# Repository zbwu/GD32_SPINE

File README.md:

# GD32_SPINE

使用GD32C103的SPIne板，和CyberDog上面的SPIne板实现兼容

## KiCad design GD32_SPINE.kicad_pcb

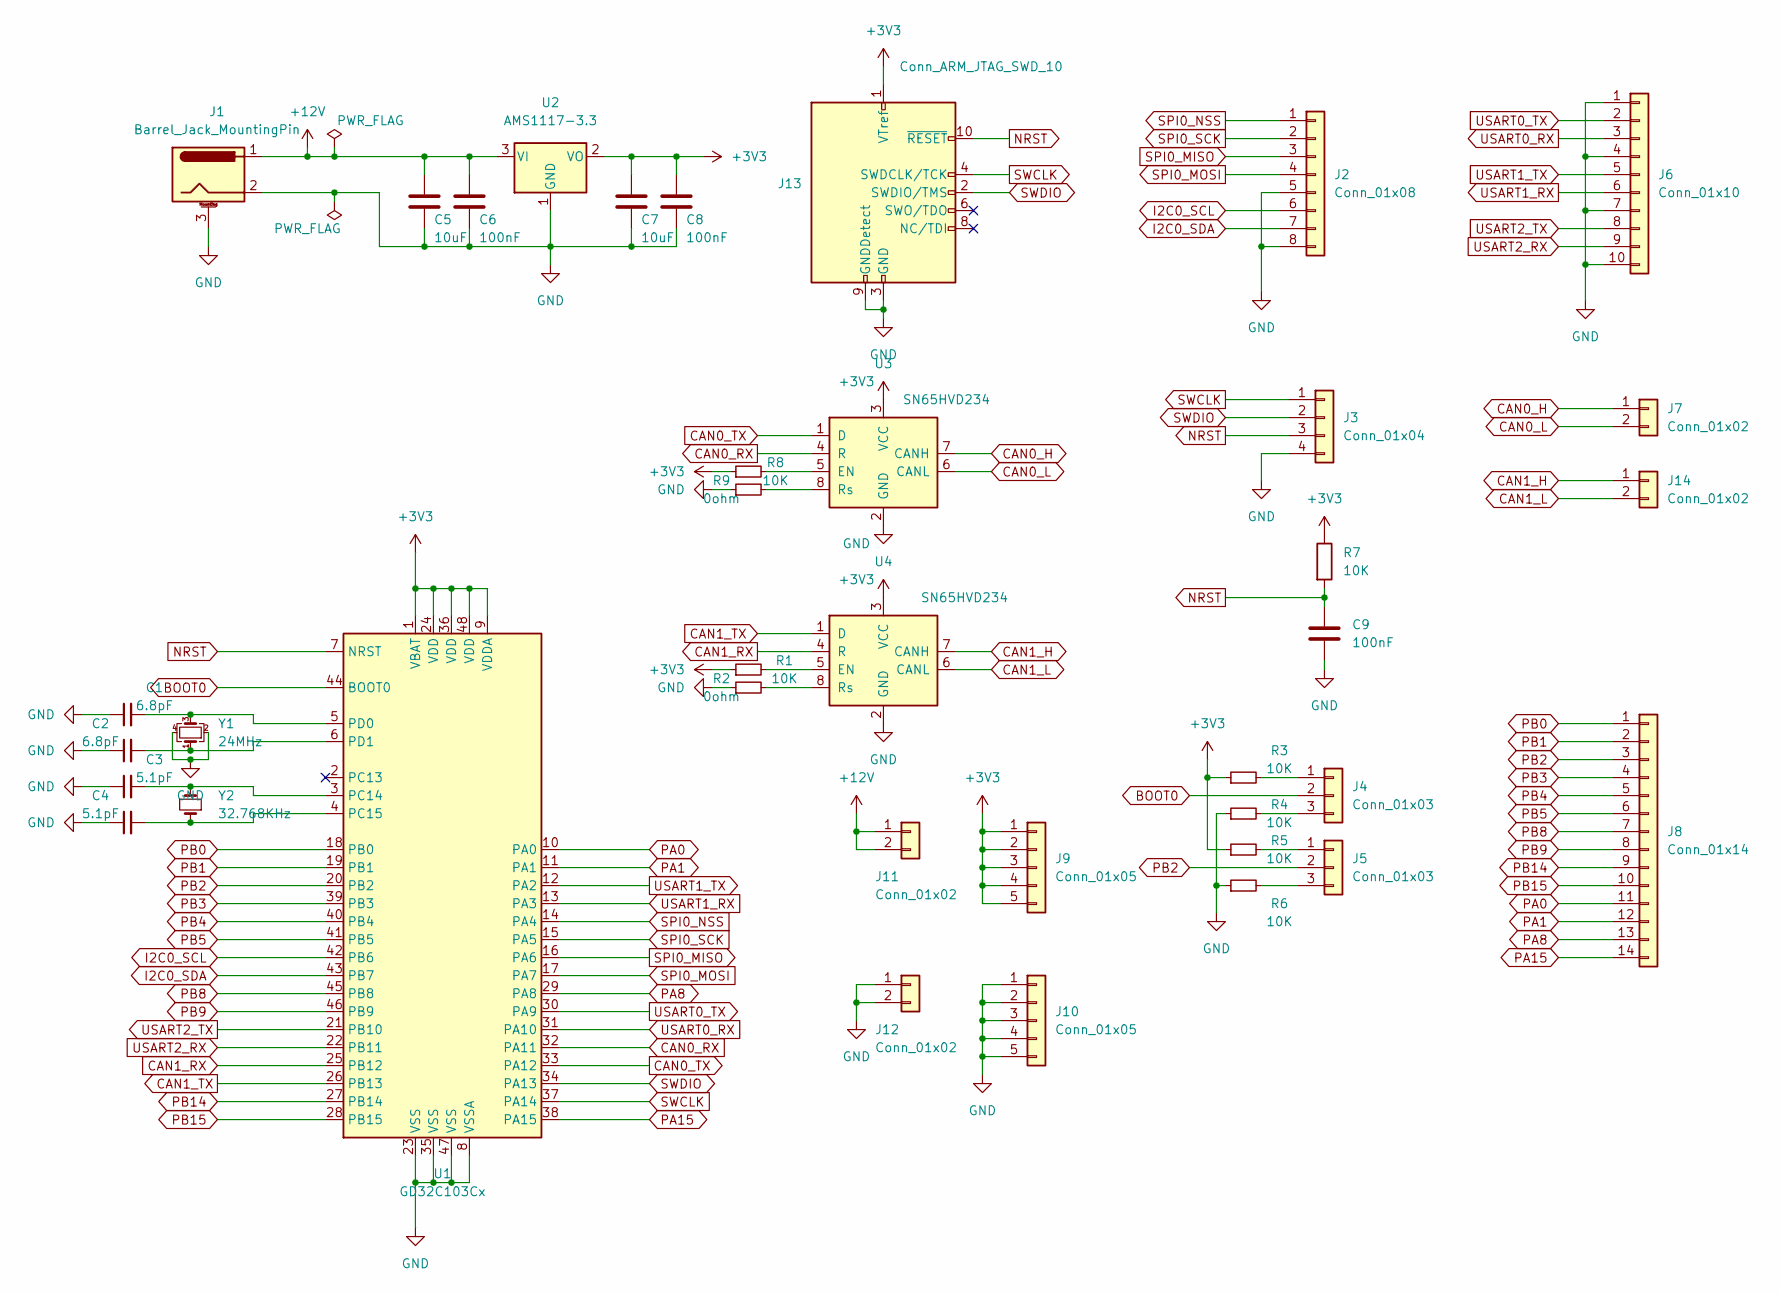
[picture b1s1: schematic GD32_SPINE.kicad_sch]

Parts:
C1, C2: 6.8pF; C_0603_1608Metric_Pad1.08x0.95mm_HandSolder
C3, C4: 5.1pF; C_0603_1608Metric_Pad1.08x0.95mm_HandSolder
C5, C7: 10uF; C_1206_3216Metric_Pad1.33x1.80mm_HandSolder
C6, C8, C9: 100nF; C_0603_1608Metric_Pad1.08x0.95mm_HandSolder
J1: Barrel_Jack_MountingPin; BarrelJack_GCT_DCJ200-10-A_Horizontal
J2: Conn_01x08; PinHeader_1x08_P2.54mm_Vertical
J3: Conn_01x04; PinHeader_1x04_P2.54mm_Vertical
J4, J5: Conn_01x03; PinHeader_1x03_P2.54mm_Vertical
J6: Conn_01x10; PinHeader_1x10_P2.54mm_Vertical
J7, J11, J12, J14: Conn_01x02; PinHeader_1x02_P2.54mm_Vertical
J8: Conn_01x14; PinHeader_1x14_P2.54mm_Vertical
J9, J10: Conn_01x05; PinHeader_1x05_P2.54mm_Vertical
J13: Conn_ARM_JTAG_SWD_10; PinHeader_2x05_P1.27mm_Vertical
R1, R3, R4, R5, R6, R7, R8: 10K; C_0603_1608Metric_Pad1.08x0.95mm_HandSolder
R2, R9: 0ohm; C_0603_1608Metric_Pad1.08x0.95mm_HandSolder
U1: GD32C103Cx; LQFP-48_7x7mm_P0.5mm
U2: AMS1117-3.3; SOT-223-3_TabPin2
U3, U4: SN65HVD234; SOIC-8_3.9x4.9mm_P1.27mm
Y1: 24MHz; Crystal_SMD_3225-4Pin_3.2x2.5mm
Y2: 32.768KHz; Crystal_SMD_3215-2Pin_3.2x1.5mm

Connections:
+3V3: C7.1, C8.1, J9.1, J9.2, J9.3, J9.4, J9.5, J13.1 (VTref), R1.1, R3.1, R5.1, R7.1, R8.1, U1.1 (VBAT), U1.9 (VDDA), U1.24 (VDD), U1.36 (VDD), U1.48 (VDD), U2.2 (VO), U3.3 (VCC), U4.3 (VCC)
+12V: C5.1, C6.1, J1.1, J11.1, J11.2, U2.3 (VI)
BOOT0: J4.2, U1.44 (BOOT0)
CAN0_H: J7.1, U3.7 (CANH)
CAN0_L: J7.2, U3.6 (CANL)
CAN0_RX: U1.32 (PA11), U3.4 (R)
CAN0_TX: U1.33 (PA12), U3.1 (D)
CAN1_H: J14.1, U4.7 (CANH)
CAN1_L: J14.2, U4.6 (CANL)
CAN1_RX: U1.25 (PB12), U4.4 (R)
CAN1_TX: U1.26 (PB13), U4.1 (D)
GND: C1.1, C2.1, C3.1, C4.1, C5.2, C6.2, C7.2, C8.2, C9.2, J1.2, J1.3, J2.5, J2.8, J3.4, J6.1, J6.4, J6.7, J6.10, J10.1, J10.2, J10.3, J10.4, J10.5, J12.1, J12.2, J13.3 (GND), J13.5 (GND), J13.9 (GNDDetect), R2.1, R4.1, R6.1, R9.1, U1.8 (VSSA), U1.23 (VSS), U1.35 (VSS), U1.47 (VSS), U2.1 (GND), U3.2 (GND), U4.2 (GND), Y1.2, Y1.4
I2C0_SCL: J2.6, U1.42 (PB6)
I2C0_SDA: J2.7, U1.43 (PB7)
NRST: C9.1, J3.3, J13.10 (~RESET), R7.2, U1.7 (NRST)
unnamed: C1.2, U1.5 (PD0), Y1.3
unnamed: C2.2, U1.6 (PD1), Y1.1
unnamed: C3.2, U1.3 (PC14), Y2.2
unnamed: C4.2, U1.4 (PC15), Y2.1
unnamed: J4.1, R3.2
unnamed: J4.3, R4.2
unnamed: J5.1, R5.2
unnamed: J5.3, R6.2
unnamed: R1.2, U4.5 (EN)
unnamed: R2.2, U4.8 (Rs)
unnamed: R8.2, U3.5 (EN)
unnamed: R9.2, U3.8 (Rs)
PA0: J8.11, U1.10 (PA0)
PA1: J8.12, U1.11 (PA1)
PA8: J8.13, U1.29 (PA8)
PA15: J8.14, U1.38 (PA15)
PB0: J8.1, U1.18 (PB0)
PB1: J8.2, U1.19 (PB1)
PB2: J5.2, J8.3, U1.20 (PB2)
PB3: J8.4, U1.39 (PB3)
PB4: J8.5, U1.40 (PB4)
PB5: J8.6, U1.41 (PB5)
PB8: J8.7, U1.45 (PB8)
PB9: J8.8, U1.46 (PB9)
PB14: J8.9, U1.27 (PB14)
PB15: J8.10, U1.28 (PB15)
SPI0_MISO: J2.3, U1.16 (PA6)
SPI0_MOSI: J2.4, U1.17 (PA7)
SPI0_NSS: J2.1, U1.14 (PA4)
SPI0_SCK: J2.2, U1.15 (PA5)
SWCLK: J3.1, J13.4 (SWDCLK/TCK), U1.37 (PA14)
SWDIO: J3.2, J13.2 (SWDIO/TMS), U1.34 (PA13)
USART0_RX: J6.3, U1.31 (PA10)
USART0_TX: J6.2, U1.30 (PA9)
USART1_RX: J6.6, U1.13 (PA3)
USART1_TX: J6.5, U1.12 (PA2)
USART2_RX: J6.9, U1.22 (PB11)
USART2_TX: J6.8, U1.21 (PB10)

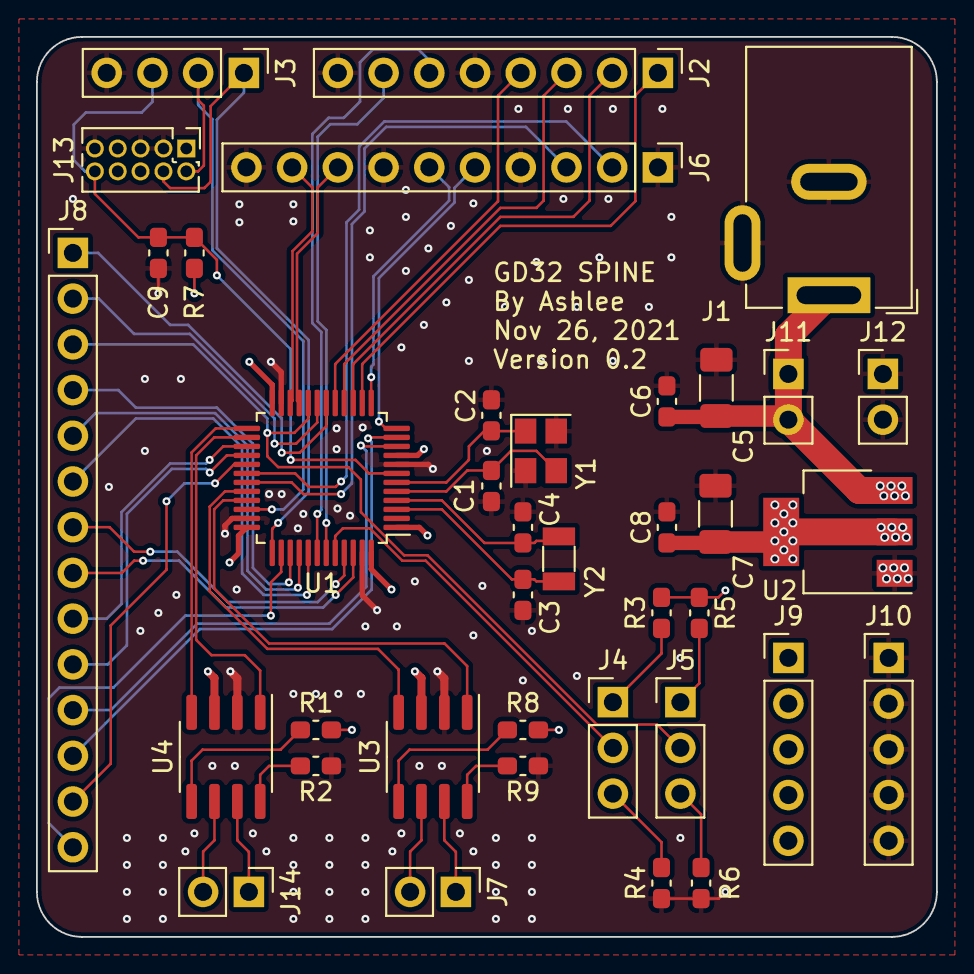
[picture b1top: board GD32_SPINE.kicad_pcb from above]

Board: 4 copper layers, 50.0 x 50.0 mm, 38 parts (0 on the bottom side), 53 nets.

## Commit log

2021-10-23 initial version 0.1
2021-10-23 add pcb screenshot and sch pdf
2021-10-23 Update README.md
    add note
2021-11-30 version 0.2
